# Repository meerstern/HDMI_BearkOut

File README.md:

# HDMI_BearkOut
Breakout board of TFP410

TFP410ブレイクアウトボードはデジタルRGB信号をTFP410でDVI/HDMI出力に変換する変換基板です。
FPGA/CPLDからデジタルRGB信号を出力してDVI/HDMIディスプレイに映す場合に使用します。
RGB24bit(8bit x3)に対応しています。

MIT Lisense

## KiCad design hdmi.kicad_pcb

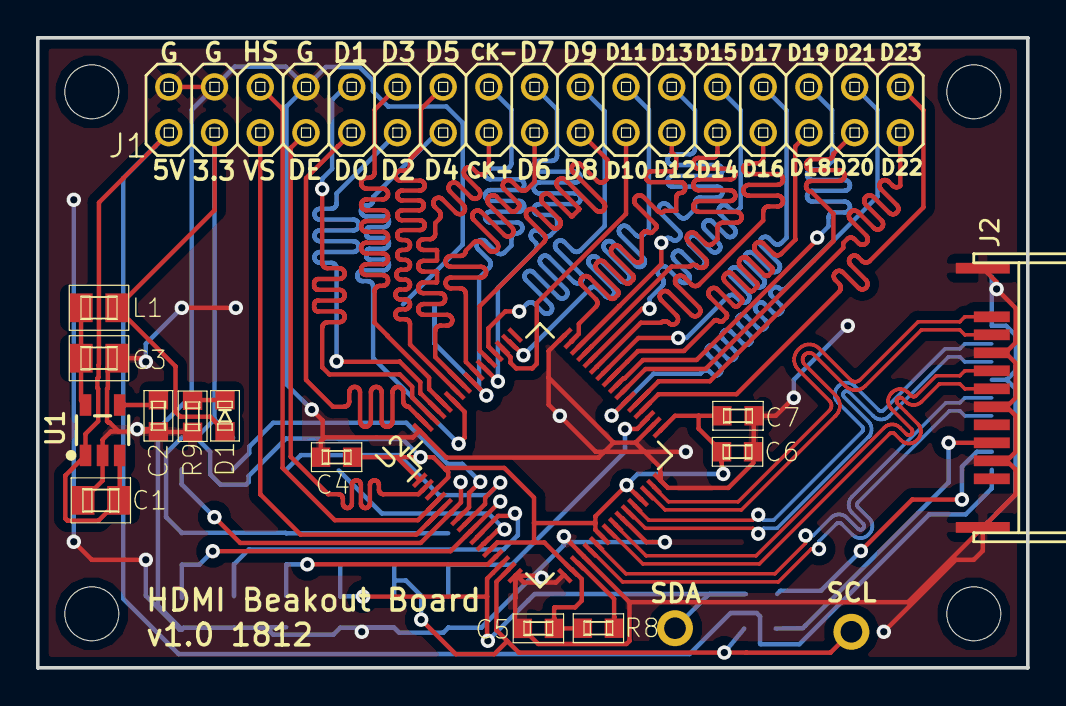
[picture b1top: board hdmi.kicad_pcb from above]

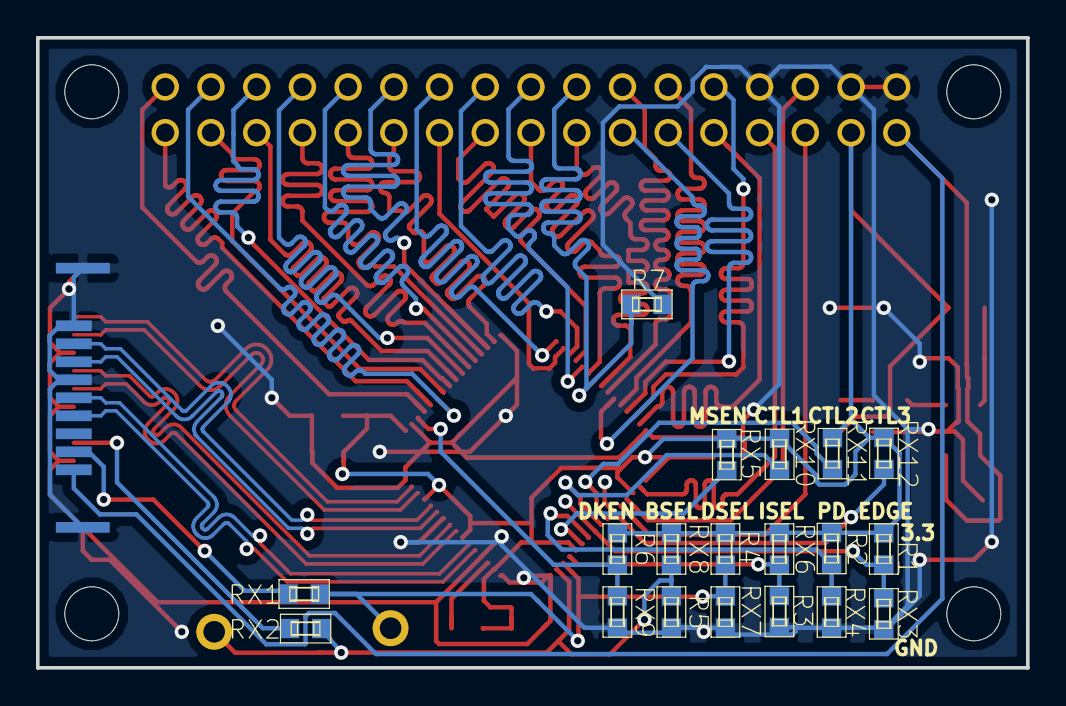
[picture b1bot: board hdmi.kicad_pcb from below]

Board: 2 copper layers, 55.0 x 35.0 mm, 40 parts (19 on the bottom side), 56 nets.

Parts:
C1, C3: 10u; generic-SMD2012
C2, C4, C5, C6, C7: 0.01u; generic-SMD1608
D1: LED; generic-LED1608
J1: Conn_02x17_Odd_Even; pinhead-2X17
J2: HDMI_A; HDMICON
L1: L; generic-SMD2012
R1, R2, R3, R4, R5, R6: 20k; generic-SMD1608
R7: 0; generic-SMD1608
R8: 500; generic-SMD1608
R9: 1k; generic-SMD1608
REF1, REF2, REF3, REF4: MountingHole_3mm
RX1, RX2: 0; generic-SMD1608
RX3, RX4, RX5, RX6, RX7, RX8, RX9, RX10, RX11, RX12: 20k; generic-SMD1608
TP1, TP2: TestPoint; CONN_1
U1: LD3985M33R_SOT23; SOT23-5
U2: TFP410; LQFP-64_10x10mm_Pitch0.5mm

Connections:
+3V3: C4.1, C5.1, C6.1, C7.1, D1.A, J1.3, L1.2, R1.2, R2.2, R4.2, R6.2, R8.2, RX5.2, RX6.2, RX8.2, RX10.2, RX11.2, RX12.2, U2.1, U2.3, U2.12, U2.18, U2.23, U2.29, U2.33
/5V: C1.1, J1.1, J2.18, U1.1, U1.3
/BSEL: R5.2, RX2.2, RX8.1, TP2.1, U2.15
/CK+: J2.10, U2.22
/CK-: J2.12, U2.21
/CTL1: RX10.1, U2.8
/CTL2: RX11.1, U2.7
/CTL3: RX12.1, U2.6
/D0+: J2.7, U2.25
/D0-: J2.9, U2.24
/D1+: J2.4, U2.28
/D1-: J2.6, U2.27
/D2+: J2.1, U2.31
/D2-: J2.3, U2.30
/DATA0: J1.9, U2.63
/DATA1: J1.10, U2.62
/DATA2: J1.11, U2.61
/DATA3: J1.12, U2.60
/DATA4: J1.13, U2.59
/DATA5: J1.14, U2.58
/DATA6: J1.17, U2.55
/DATA7: J1.18, U2.54
/DATA8: J1.19, U2.53
/DATA9: J1.20, U2.52
/DATA10: J1.21, U2.51
/DATA11: J1.22, U2.50
/DATA12: J1.23, U2.47
/DATA13: J1.24, U2.46
/DATA14: J1.25, U2.45
/DATA15: J1.26, U2.44
/DATA16: J1.27, U2.43
/DATA17: J1.28, U2.42
/DATA18: J1.29, U2.41
/DATA19: J1.30, U2.40
/DATA20: J1.31, U2.39
/DATA21: J1.32, U2.38
/DATA22: J1.33, U2.37
/DATA23: J1.34, U2.36
/DE: J1.7, U2.2
/DKEN: R6.1, RX9.2, U2.35
/DSEL: R4.1, RX1.2, RX7.2, TP1.1, U2.14
/EDGE: R1.1, RX3.2, U2.9
/HSYNC: J1.6, U2.4
/IDCK+: J1.15, U2.57
/IDCK-: J1.16, R7.1, U2.56
/ISEL: R3.2, RX6.1, U2.13
/MSEN: RX5.1, U2.11
/PD: R2.1, RX4.2, U2.10
/SCL: J2.15, RX2.1
/SDA: J2.16, RX1.1
/VSYNC: J1.5, U2.5
GND: C1.2, C2.2, C3.2, C4.2, C5.2, C6.2, C7.2, J1.2, J1.4, J1.8, J2.2, J2.5, J2.8, J2.11, J2.17, J2.SH, R3.1, R5.1, R7.2, R9.1, RX3.1, RX4.1, RX7.1, RX9.1, U1.2, U2.16, U2.17, U2.20, U2.26, U2.32, U2.34, U2.48, U2.64
unnamed: C2.1, U1.4
unnamed: C3.1, L1.1, U1.5
unnamed: D1.K, R9.2
unnamed: R8.1, U2.19

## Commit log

2019-01-19 Init
2019-02-23 Del files
2020-11-08 Add sample fpga files
